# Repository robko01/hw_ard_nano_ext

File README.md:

# hw_ard_nano_ext
This repo is holding design files for Robko01, Arduino Nano extension.

The board is designed in KiCAD.

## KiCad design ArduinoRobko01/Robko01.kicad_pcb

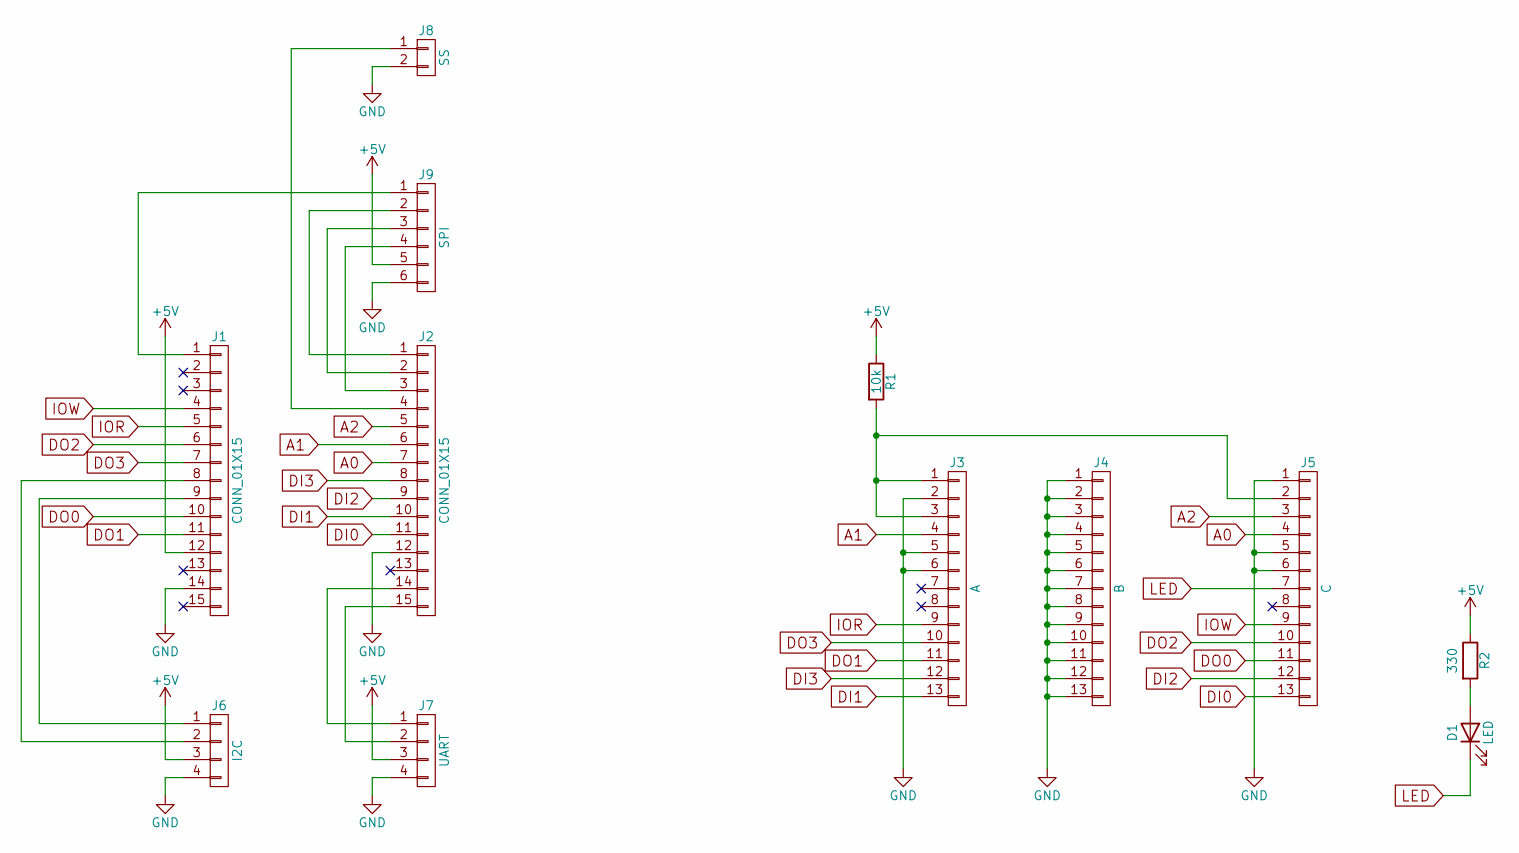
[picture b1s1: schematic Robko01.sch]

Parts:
D1: LED; LED_D3.0mm
J1, J2: CONN_01X15; SL-115-X-XX_1x15
J3: A; SL-113-X-XX_1x13
J4: B; SL-113-X-XX_1x13
J5: C; SL-113-X-XX_1x13
J6: I2C; SL-104-X-XX_1x04
J7: UART; SL-104-X-XX_1x04
J8: SS; SL-102-X-XX_1x02
J9: SPI; SL-106-X-XX_1x06
R1: 10k; R_Axial_DIN0204_L3.6mm_D1.6mm_P5.08mm_Horizontal
R2: 330; R_Axial_DIN0207_L6.3mm_D2.5mm_P10.16mm_Horizontal

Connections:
+5V: J1.12, J6.3, J7.3, J9.5, R1.1, R2.1
A0: J2.7, J5.4
A1: J2.6, J3.4
A2: J2.5, J5.3
DI0: J2.11, J5.13
DI1: J2.10, J3.13
DI2: J2.9, J5.12
DI3: J2.8, J3.12
DO0: J1.10, J5.11
DO1: J1.11, J3.11
DO2: J1.6, J5.10
DO3: J1.7, J3.10
GND: J1.14, J2.12, J3.2, J3.5, J3.6, J4.1, J4.2, J4.3, J4.4, J4.5, J4.6, J4.7, J4.8, J4.9, J4.10, J4.11, J4.12, J4.13, J5.1, J5.5, J5.6, J6.4, J7.4, J8.2, J9.6
IOR: J1.5, J3.9
IOW: J1.4, J5.9
LED: D1.1 (K), J5.7
unnamed: D1.2 (A), R2.2
unnamed: J1.1, J9.1
unnamed: J1.8, J6.2
unnamed: J1.9, J6.1
unnamed: J2.1, J9.2
unnamed: J2.2, J9.3
unnamed: J2.3, J9.4
unnamed: J2.4, J8.1
unnamed: J2.14, J7.1
unnamed: J2.15, J7.2
unnamed: J3.1, J3.3, J5.2, R1.2

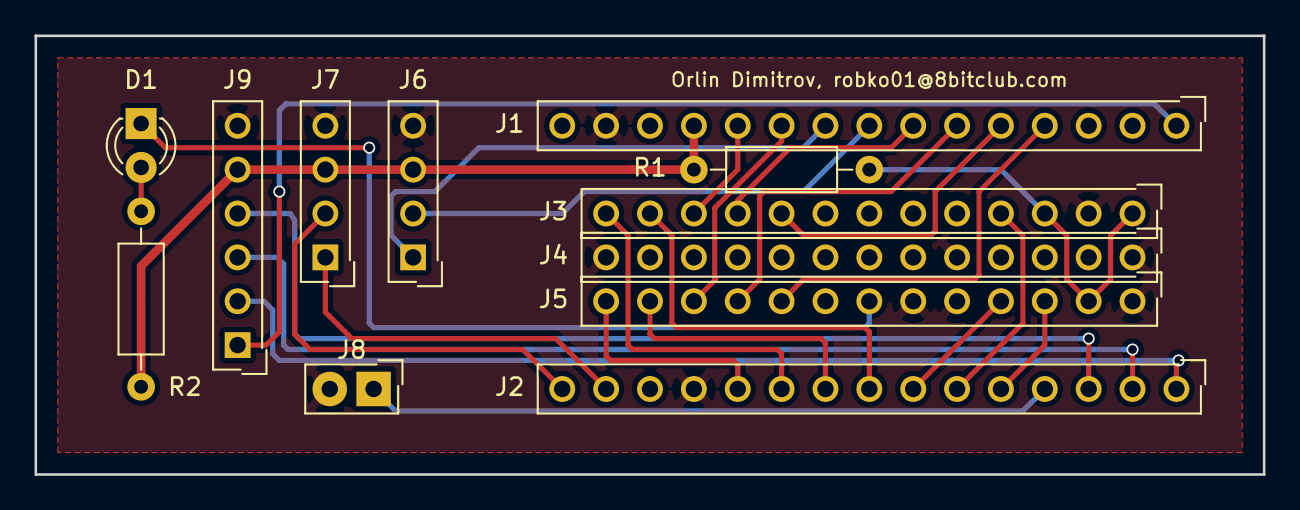
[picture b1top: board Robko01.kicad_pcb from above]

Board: 2 copper layers, 71.1 x 25.4 mm, 12 parts (0 on the bottom side), 27 nets.

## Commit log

2020-08-17 Add design files
2020-08-30 Add ignore file
2020-08-30 Fix typo
2021-11-16 Fix main VRM mount holes, connectors naming and labels
2021-11-16 Update net list
